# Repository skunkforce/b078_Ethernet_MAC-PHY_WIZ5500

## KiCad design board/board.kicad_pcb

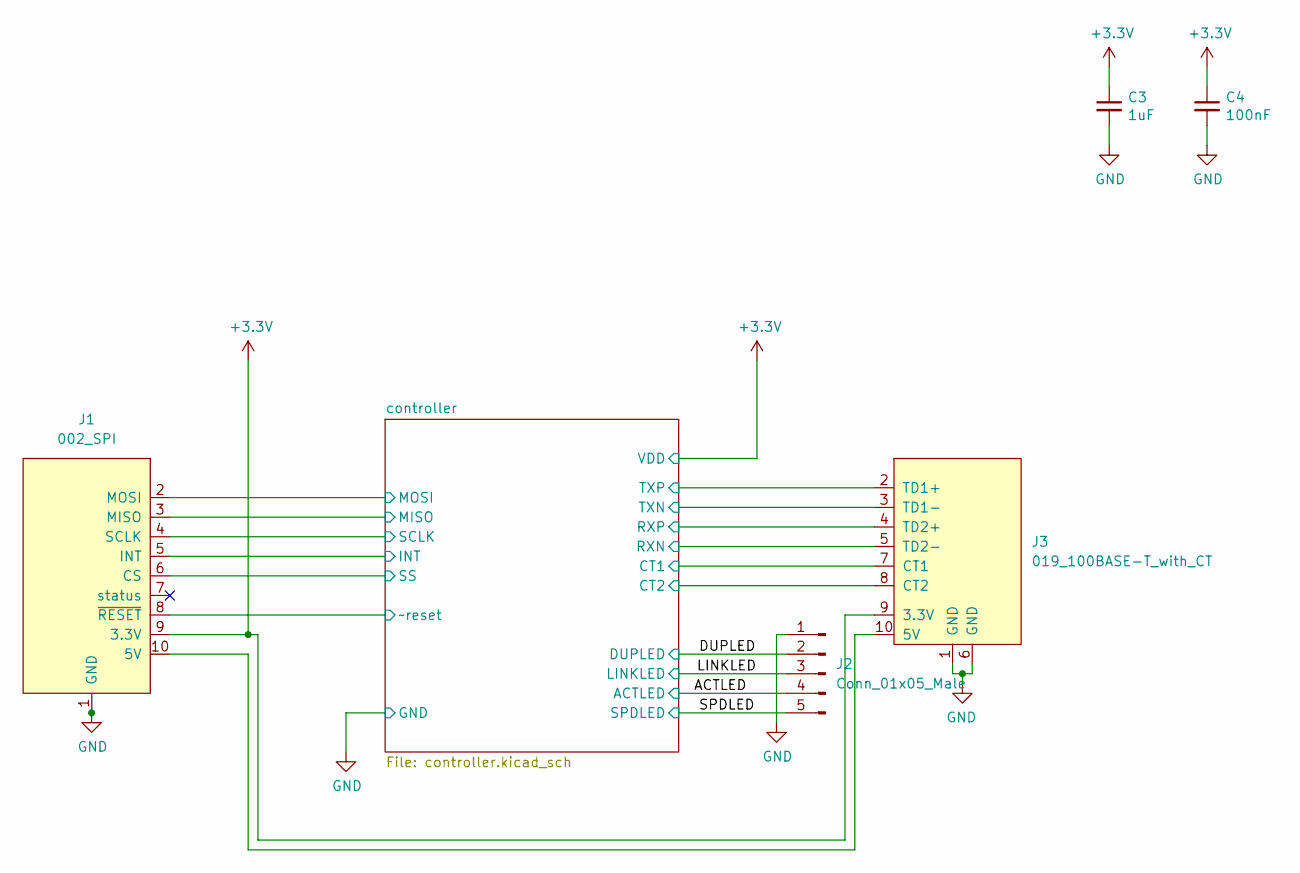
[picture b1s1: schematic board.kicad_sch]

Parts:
C3: 1uF; C_0603_1608Metric; Voltage 6.3V
C4: 100nF; C_0603_1608Metric; Voltage 6.3V
J1: 002_SPI; on_edge_2x05_device
J2: Conn_01x05_Male; PinHeader_1x05_P2.54mm_Vertical
J3: 019_100BASE-T_with_CT; on_edge_2x05_host

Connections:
+3.3V: C3.1, C4.1, J1.9 (3.3V), J3.9 (3.3V); also elsewhere on the board
/ACTLED: J2.4; also elsewhere on the board
/DUPLED: J2.2; also elsewhere on the board
/LINKLED: J2.3; also elsewhere on the board
/SPDLED: J2.5; also elsewhere on the board
/controller/CT1: J3.7 (CT1); also elsewhere on the board
/controller/CT2: J3.8 (CT2); also elsewhere on the board
/controller/INT: J1.5 (INT); also elsewhere on the board
/controller/MISO: J1.3 (MISO); also elsewhere on the board
/controller/MOSI: J1.2 (MOSI); also elsewhere on the board
/controller/RXN: J3.5 (TD2-); also elsewhere on the board
/controller/RXP: J3.4 (TD2+); also elsewhere on the board
/controller/SCLK: J1.4 (SCLK); also elsewhere on the board
/controller/SS: J1.6 (CS); also elsewhere on the board
/controller/TXN: J3.3 (TD1-); also elsewhere on the board
/controller/TXP: J3.2 (TD1+); also elsewhere on the board
/controller/~reset: J1.8 (~RESET); also elsewhere on the board
GND: C3.2, C4.2, J1.1 (GND), J2.1, J3.1 (GND), J3.6 (GND); also elsewhere on the board
unnamed: J1.10 (5V), J3.10 (5V)

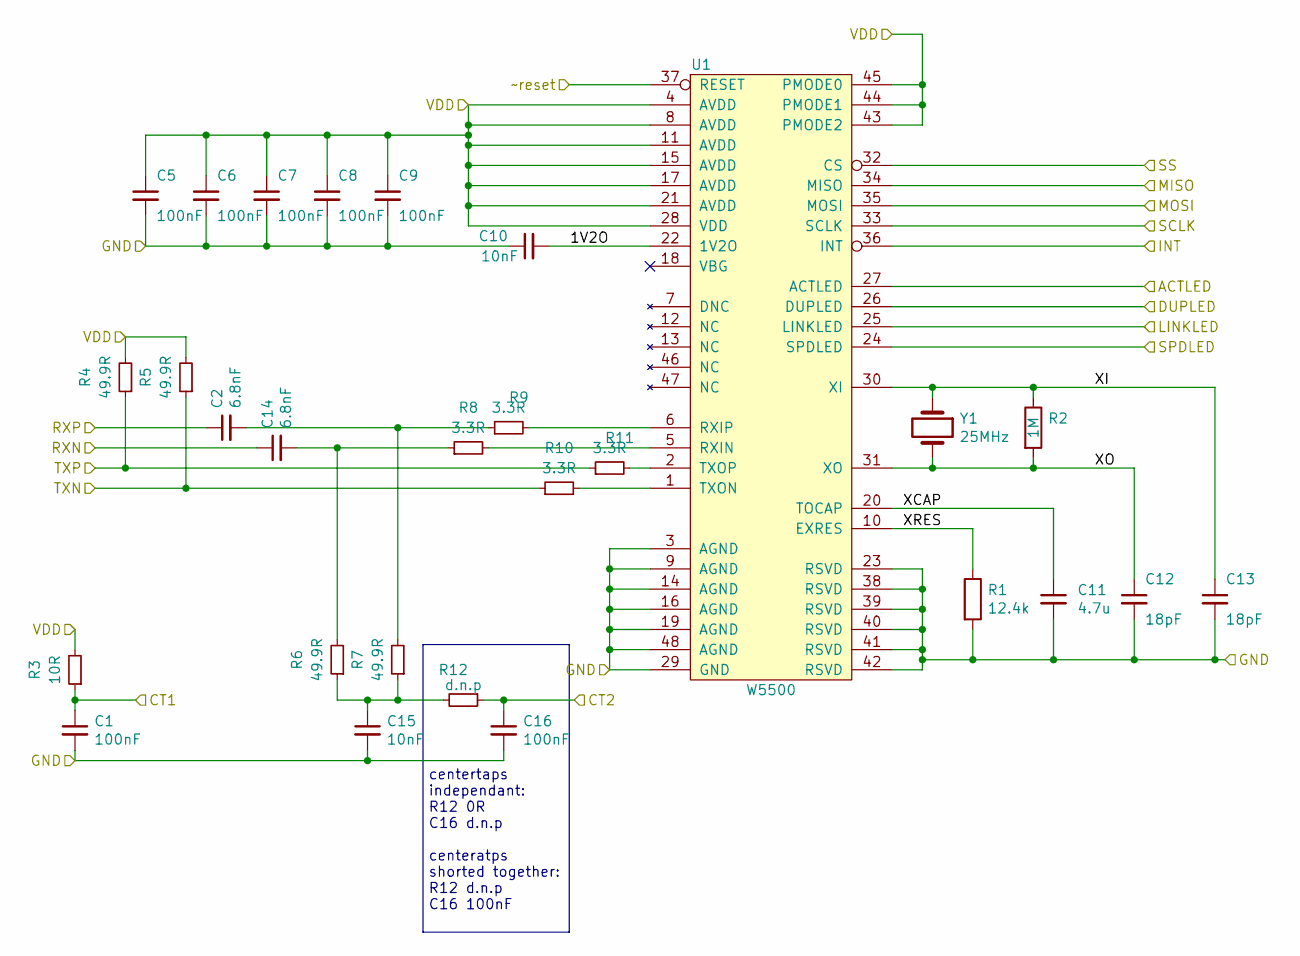
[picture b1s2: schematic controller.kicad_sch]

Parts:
C1, C16: 100nF; C_0603_1608Metric; Voltage 6.3V
C2, C14: 6.8nF; C_0603_1608Metric; Voltage 6.3V
C5, C6, C7, C8, C9: 100nF; C_0603_1608Metric; DigiKey Part Number 1276-1012-1-ND
C10: 10nF; C_0603_1608Metric; DigiKey Part Number 1276-1921-1-ND
C11: 4.7u; C_0603_1608Metric; DigiKey Part Number 1276-1907-1-ND
C12, C13: 18pF; C_0603_1608Metric; DigiKey Part Number 1276-1089-1-ND
C15: 10nF; C_0603_1608Metric; Voltage 6.3V
R1: 12.4k; R_0603_1608Metric; Tolerance ±1%; DigiKey Part Number 311-12.4KHRCT-ND
R2: 1M; R_0603_1608Metric; DigiKey Part Number 311-1.0MGRCT-ND
R3: 10R; R_0805_2012Metric
R4, R5, R6, R7: 49.9R; R_0805_2012Metric
R8, R9, R10, R11: 3.3R; R_0603_1608Metric
R12: d.n.p; R_0805_2012Metric
U1: W5500; LQFP-48_7x7mm_P0.5mm; DigiKey Part Number 1278-1021-ND
Y1: 25MHz; Crystal_SMD_5032-2Pin_5.0x3.2mm; MPN 445I23D25M00000; DigiKey Part Number CTX1175TR-ND

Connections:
+3.3V: C5.1, C6.1, C7.1, C8.1, C9.1, R3.2, R4.2, R5.2, U1.4 (AVDD), U1.8 (AVDD), U1.11 (AVDD), U1.15 (AVDD), U1.17 (AVDD), U1.21 (AVDD), U1.28 (VDD), U1.43 (PMODE2), U1.44 (PMODE1), U1.45 (PMODE0); also elsewhere on the board
/ACTLED: U1.27 (ACTLED); also elsewhere on the board
/DUPLED: U1.26 (DUPLED); also elsewhere on the board
/LINKLED: U1.25 (LINKLED); also elsewhere on the board
/SPDLED: U1.24 (SPDLED); also elsewhere on the board
/controller/1V2O: C10.2, U1.22 (1V2O)
/controller/CT1: C1.1, R3.1; also elsewhere on the board
/controller/CT2: C16.1, R12.1; also elsewhere on the board
/controller/INT: U1.36 (INT); also elsewhere on the board
/controller/MISO: U1.34 (MISO); also elsewhere on the board
/controller/MOSI: U1.35 (MOSI); also elsewhere on the board
/controller/RXN: C14.1; also elsewhere on the board
/controller/RXP: C2.1; also elsewhere on the board
/controller/SCLK: U1.33 (SCLK); also elsewhere on the board
/controller/SS: U1.32 (CS); also elsewhere on the board
/controller/TXN: R5.1, R10.1; also elsewhere on the board
/controller/TXP: R4.1, R11.1; also elsewhere on the board
/controller/XCAP: C11.1, U1.20 (TOCAP)
/controller/XI: C13.1, R2.1, U1.30 (XI), Y1.1
/controller/XO: C12.1, R2.2, U1.31 (XO), Y1.2
/controller/XRES: R1.1, U1.10 (EXRES)
/controller/~reset: U1.37 (RESET); also elsewhere on the board
GND: C1.2, C5.2, C6.2, C7.2, C8.2, C9.2, C10.1, C11.2, C12.2, C13.2, C15.2, C16.2, R1.2, U1.3 (AGND), U1.9 (AGND), U1.14 (AGND), U1.16 (AGND), U1.19 (AGND), U1.23 (RSVD), U1.29 (GND), U1.38 (RSVD), U1.39 (RSVD), U1.40 (RSVD), U1.41 (RSVD), U1.42 (RSVD), U1.48 (AGND); also elsewhere on the board
unnamed: C2.2, R7.2, R9.1
unnamed: C14.2, R6.2, R8.1
unnamed: C15.1, R6.1, R7.1, R12.2
unnamed: R8.2, U1.5 (RXIN)
unnamed: R9.2, U1.6 (RXIP)
unnamed: R10.2, U1.1 (TXON)
unnamed: R11.2, U1.2 (TXOP)

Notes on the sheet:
centertaps independant: R12 0R C16 d.n.p centeratps shorted together: R12 d.n.p C16 100nF

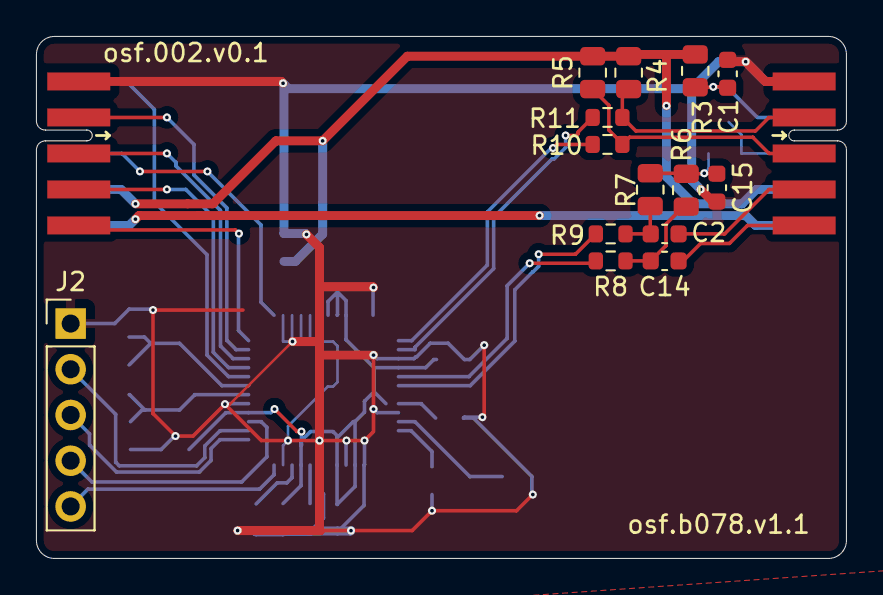
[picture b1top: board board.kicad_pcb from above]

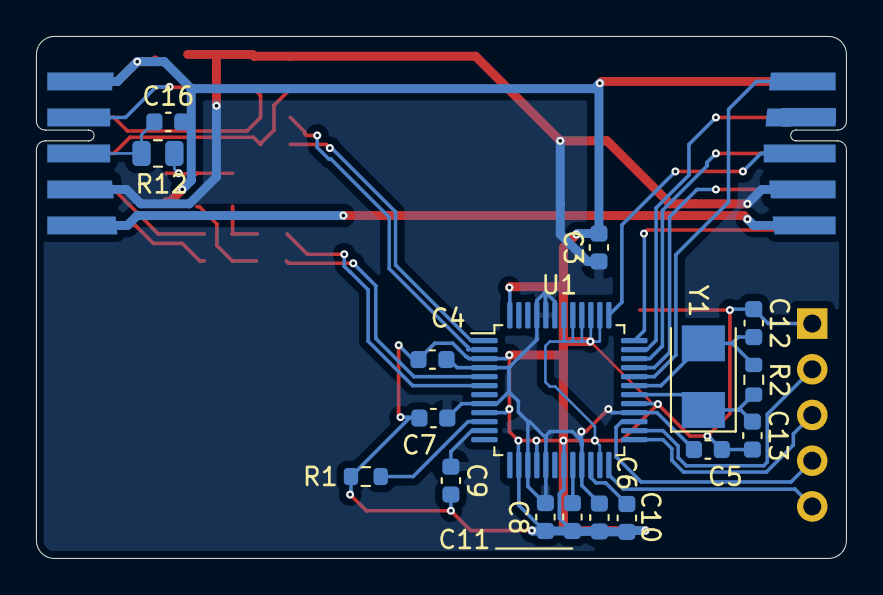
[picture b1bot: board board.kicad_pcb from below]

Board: 2 copper layers, 45.0 x 29.0 mm, 33 parts (17 on the bottom side), 31 nets.

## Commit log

2023-02-27 initial
2023-03-08 broke out all leds in external connector
2023-05-09 added option for shorted center taps
